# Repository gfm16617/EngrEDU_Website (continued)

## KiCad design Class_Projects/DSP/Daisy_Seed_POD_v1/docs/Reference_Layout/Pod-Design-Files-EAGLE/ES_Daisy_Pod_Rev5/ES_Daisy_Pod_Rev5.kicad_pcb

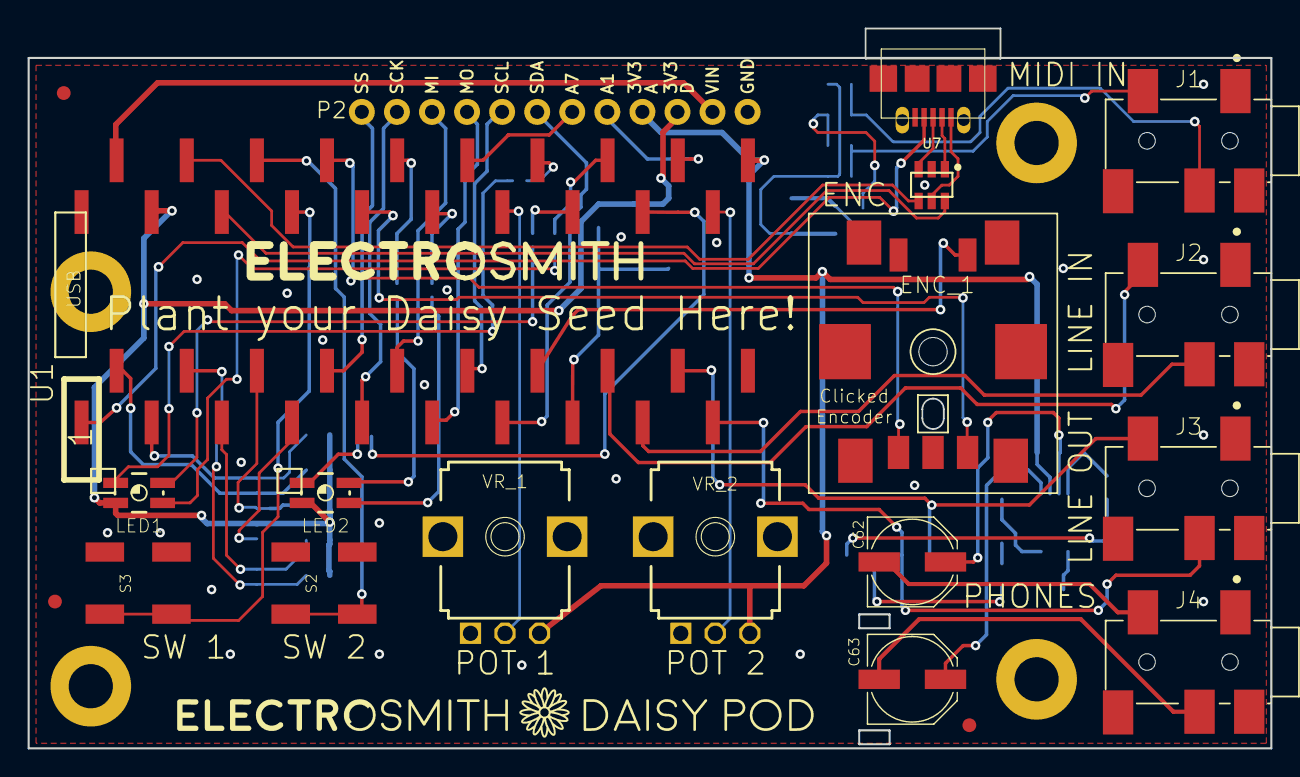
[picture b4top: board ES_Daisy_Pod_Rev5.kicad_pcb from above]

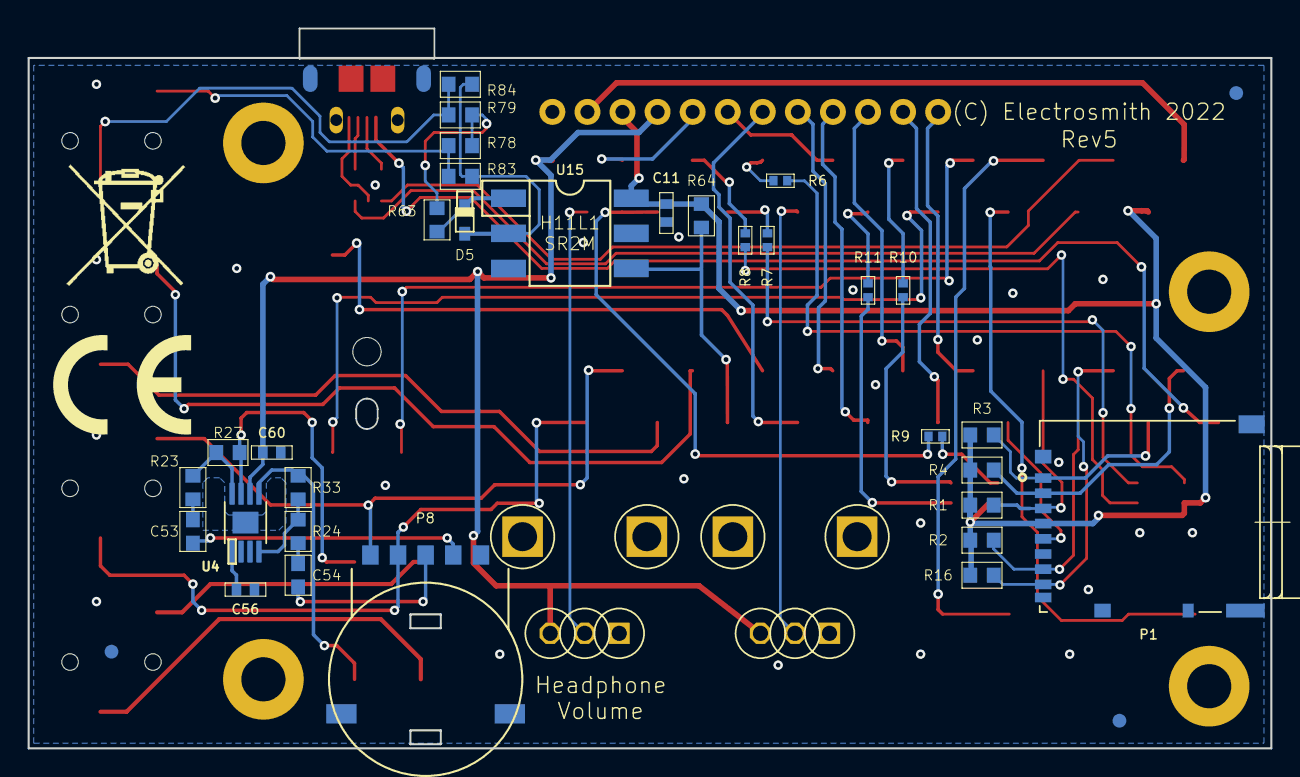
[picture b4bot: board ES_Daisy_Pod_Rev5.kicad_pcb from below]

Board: 2 copper layers, 90.0 x 52.1 mm, 62 parts (36 on the bottom side), 64 nets.

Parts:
C11, C56, C60: 100NF; C0402
C53, C54: 470NF; C0603
C62, C63: 100UF PANASONIC D8; PANASONIC_D
D5: NSR1020MW2T3G; SOD-323F
ENC_1: PEC11 Clicked Encoder; VH1-147
FD1, FD2, FD3, FD4, FD5, FD6: FIDUCIAL; FIDUCIAL_1MM
H1, H2, H3, H4: MOUNT-PAD-ROUND_3.2_NO_SILK; 32-PAD_NO_SILK
J1, J2, J3, J4: SMT Stereo 3.5mm Jack; CUI_SJ2-35863B1-SMT-TR
LED1, LED2: RGB LED SMT PLCC4; P-LCC-4-3
P1: SMT MICRO SD HORIZONTAL; HRS_DM3AT-SF-PEJM5
P2: M12_ALL_CIRCLE_DNI; 1X12_NO_SILK_ALL_CIRCLE
P5: USB MICRO SMT H-B; 47589-0001_CUT2
P8: SMT ROTARY DUAL GANG POT; RK10J12R0A0B
R1, R2, R3, R4, R16: 47K; R0603
R6, R7, R8, R9, R10, R11: 1K; R0402
R23, R24: 22K; R0603
R27, R33: 33K; R0603
R63: 220R; R0603
R64: 270R; R0603
R78, R84: DNI 0R; R0603
R79, R83: 0R; R0603
S2, S3: SMT Mini Button; TL3301SPF160QJ
U1: ES_DAISY_SEED_REV4_SMT; ES_DAISY_SEED_SMT
U4: TPA6110 MSOP-8; MSOP_8_PWRPAD
U7: USBLC6 TVS SOT-23-6; SOT-23-6L
U15: H11L1SR2M; DIL06_GULLWING
U$2: TONNE_9X13MM
U$3: CE_10X7.3MM
U$4: DAISY_POD_BRANDING_2
U$7: ES_TEXT_3X30MM
VR_1, VR_2: P-10K-B-R-PIP; 9MM_SNAP-IN_POT_SILK_PIP

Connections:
+3V3_A: C60.2, P2.9, U1.21, U4.6, VR_1.3, VR_2.3
+3V3_D: C11.1, LED1.2, LED2.2, P1.4, P2.10, R1.2, R2.2, R3.2, R4.2, R16.2, R64.1, U1.38, U15.6
A1: P2.8, U1.23
A7: P2.7, U1.29
AUDIO_IN_L: J2.2, U1.16
AUDIO_IN_R: J2.3, U1.17
AUDIO_OUT_L: J3.2, P8.P$5, U1.18
AUDIO_OUT_R: J3.3, P8.P$4, U1.19
ENC_A: ENC_1.A, U1.33
ENC_B: ENC_1.B, U1.32
ENC_CLICK: ENC_1.E, U1.14
GND: C11.2, C56.1, C60.1, ENC_1.C, ENC_1.D, J1.1, J2.1, J3.1, J4.1, P1.6, P1.P1, P1.P2, P1.P3, P1.P4, P1.SWB, P2.12, P5.5, P8.P$1, S2.3, S2.4, S3.3, S3.4, U1.20, U1.40, U4.2, U4.3, U4.9, U7.2, U15.5, VR_1.1, VR_2.1
HEADPHONE_OUT_L: C62.-, J4.2
HEADPHONE_OUT_R: C63.-, J4.3
HEADPHONE_WIPER_L: C53.1, P8.P$2
HEADPHONE_WIPER_R: C54.1, P8.P$3
I2C_SCL: P2.5, U1.12
I2C_SDA: P2.6, U1.13
LED_1_B: R8.2, U1.25
LED_1_G: R7.2, U1.26
LED_1_R: R6.2, U1.27
LED_2_B: R11.2, U1.30
LED_2_G: R10.2, U1.31
LED_2_R: R9.2, U1.24
MIDI_IN_A: R63.2, R78.1, R79.1
MIDI_IN_B: D5.A, R83.1, R84.1, U15.2
MIDI_IN_RING: J1.3, R79.2, R84.2
MIDI_IN_TIP: J1.2, R78.2, R83.2
unnamed: LED1.1, R6.1
unnamed: LED1.4, R7.1
unnamed: LED1.3, R8.1
unnamed: LED2.1, R9.1
unnamed: LED2.4, R10.1
unnamed: LED2.3, R11.1
unnamed: C54.2, R24.2
unnamed: R23.1, R27.2, U4.8
unnamed: R24.1, R33.2, U4.4
unnamed: C53.2, R23.2
unnamed: C56.2, U4.1
unnamed: C62.+, R27.1, U4.7
unnamed: C63.+, R33.1, U4.5
unnamed: D5.C, R63.1, U15.1
POT_1: U1.28, VR_1.2
POT_2: U1.22, VR_2.2
SD_CK: P1.5, U1.7
SD_CMD: P1.3, R1.1, U1.6
SD_D0: P1.7, R2.1, U1.5
SD_D1: P1.8, R16.1, U1.4
SD_D2: P1.1, R3.1, U1.3
SD_D3: P1.2, R4.1, U1.2
SPI_MISO: P2.3, U1.10
SPI_MOSI: P2.4, U1.11
SPI_NSS: P2.1, U1.8
SPI_SCK: P2.2, U1.9
TAC_SWITCH_1: S3.1, S3.2, U1.34
TAC_SWITCH_2: S2.1, S2.2, U1.35
USART1_RX: R64.2, U1.15, U15.4
USB_OTG_FS_D+: U1.37, U7.4
USB_OTG_FS_D-: U1.36, U7.6
USB_OTG_FS_D_IN_+: P5.3, U7.3
USB_OTG_FS_D_IN_-: P5.2, U7.1
USB_OTG_FS_ID: P5.4, U1.1
USB_VBUS: P5.1, U7.5
VIN: P2.11, U1.39

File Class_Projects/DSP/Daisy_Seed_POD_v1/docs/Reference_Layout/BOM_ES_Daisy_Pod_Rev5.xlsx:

Qty | IPN | MPN | Manufacturer | Designators | Vendor Link
5 | 47K R0603 | RC0603FR-0747KL | Yageo | R3 R4 R1 R2 R16 | Mouser
1 | USB MICRO SMT H-B | 47589-0001 | Molex | P5 | Mouser
2 | SMT Mini Button | TL3301SPF160QJ | E-Switch | S2 S3 | Mouser
1 | 220R R0603 | RC0603FR-07220RL | Yageo | R63 | Mouser
1 | 270R R0603 | CRCW0603270RFKEAC | Vishay | R64 | Mouser
3 | 100NF C0402 | CC0402KPX5R8BB104 | Yageo | C11 C56 C60 | Mouser
2 | 470NF C0603 | CL10B474KA8NFNC | Samsung | C53 C54 | Mouser
2 | 22K R0603 | RC0603FR-0722KL | Yageo | R23 R24 | Mouser
2 | 33K R0603 | RC0603FR-1333KL | Yageo | R27 R33 | Mouser
2 | RGB LED SMT PLCC4 | CLVBA-FKA-CAEDH8BBB7a363 | Cree | LED1 LED2 | Mouser
6 | 1K R0402 | RC0402FR-131KL | Yageo | R6 R7 R8 R9 R10 R11 | Mouser
4 | 0R R0603 | AC0603FR-070RL | Yageo | R79 R83 R78 R84 | Mouser
1 | USBLC6 TVS SOT-23-6 | USBLC6-2SC6TR | ST Micro | U7 | DigiKey
1 | NSR1020MW2T3G | NSR1020MW2T3G | On Semi | D5 | Mouser
1 | OPTO ISOLATOR | H11L1SR2M | On Semi | U15 | Mouser
1 | TPA6110 MSOP-8 | TPA6110A2DGNR | Texas Instruments | U4 | Mouser
2 | 100UF PANASONIC D8 | EMVE350ARA101MF80G | Chemi-Co | C63 C62 | Mouser
1 | EC11 Detented SMT Encoder | PEC11J-9220F-H0015 | Bourns | ENC_1 | Mouser
4 | SMT-JACK-S-H-3.5 | SJ2-35863B1-SMT-TR | CUI | J2 J3 J4 J1 | Mouser
1 | SMT MICRO SD HORIZONTAL | DM3AT-SF-PEJM5 | Hirose | P1 | Mouser
2 | P-10K-B-R Pointer | R0904N-B10K,L-25KQ/LWS | Song Huei | VR_1 VR_2 | Thonk
1 | 1X20 FEMALE SMT 2.54MM VERTICAL | SSM-120-L-SV | Samtec | U1 | Mouser
1 | SMT ROTARY DUAL GANG POT | RK10J12R0A0B | Alps | P8 | Mouser

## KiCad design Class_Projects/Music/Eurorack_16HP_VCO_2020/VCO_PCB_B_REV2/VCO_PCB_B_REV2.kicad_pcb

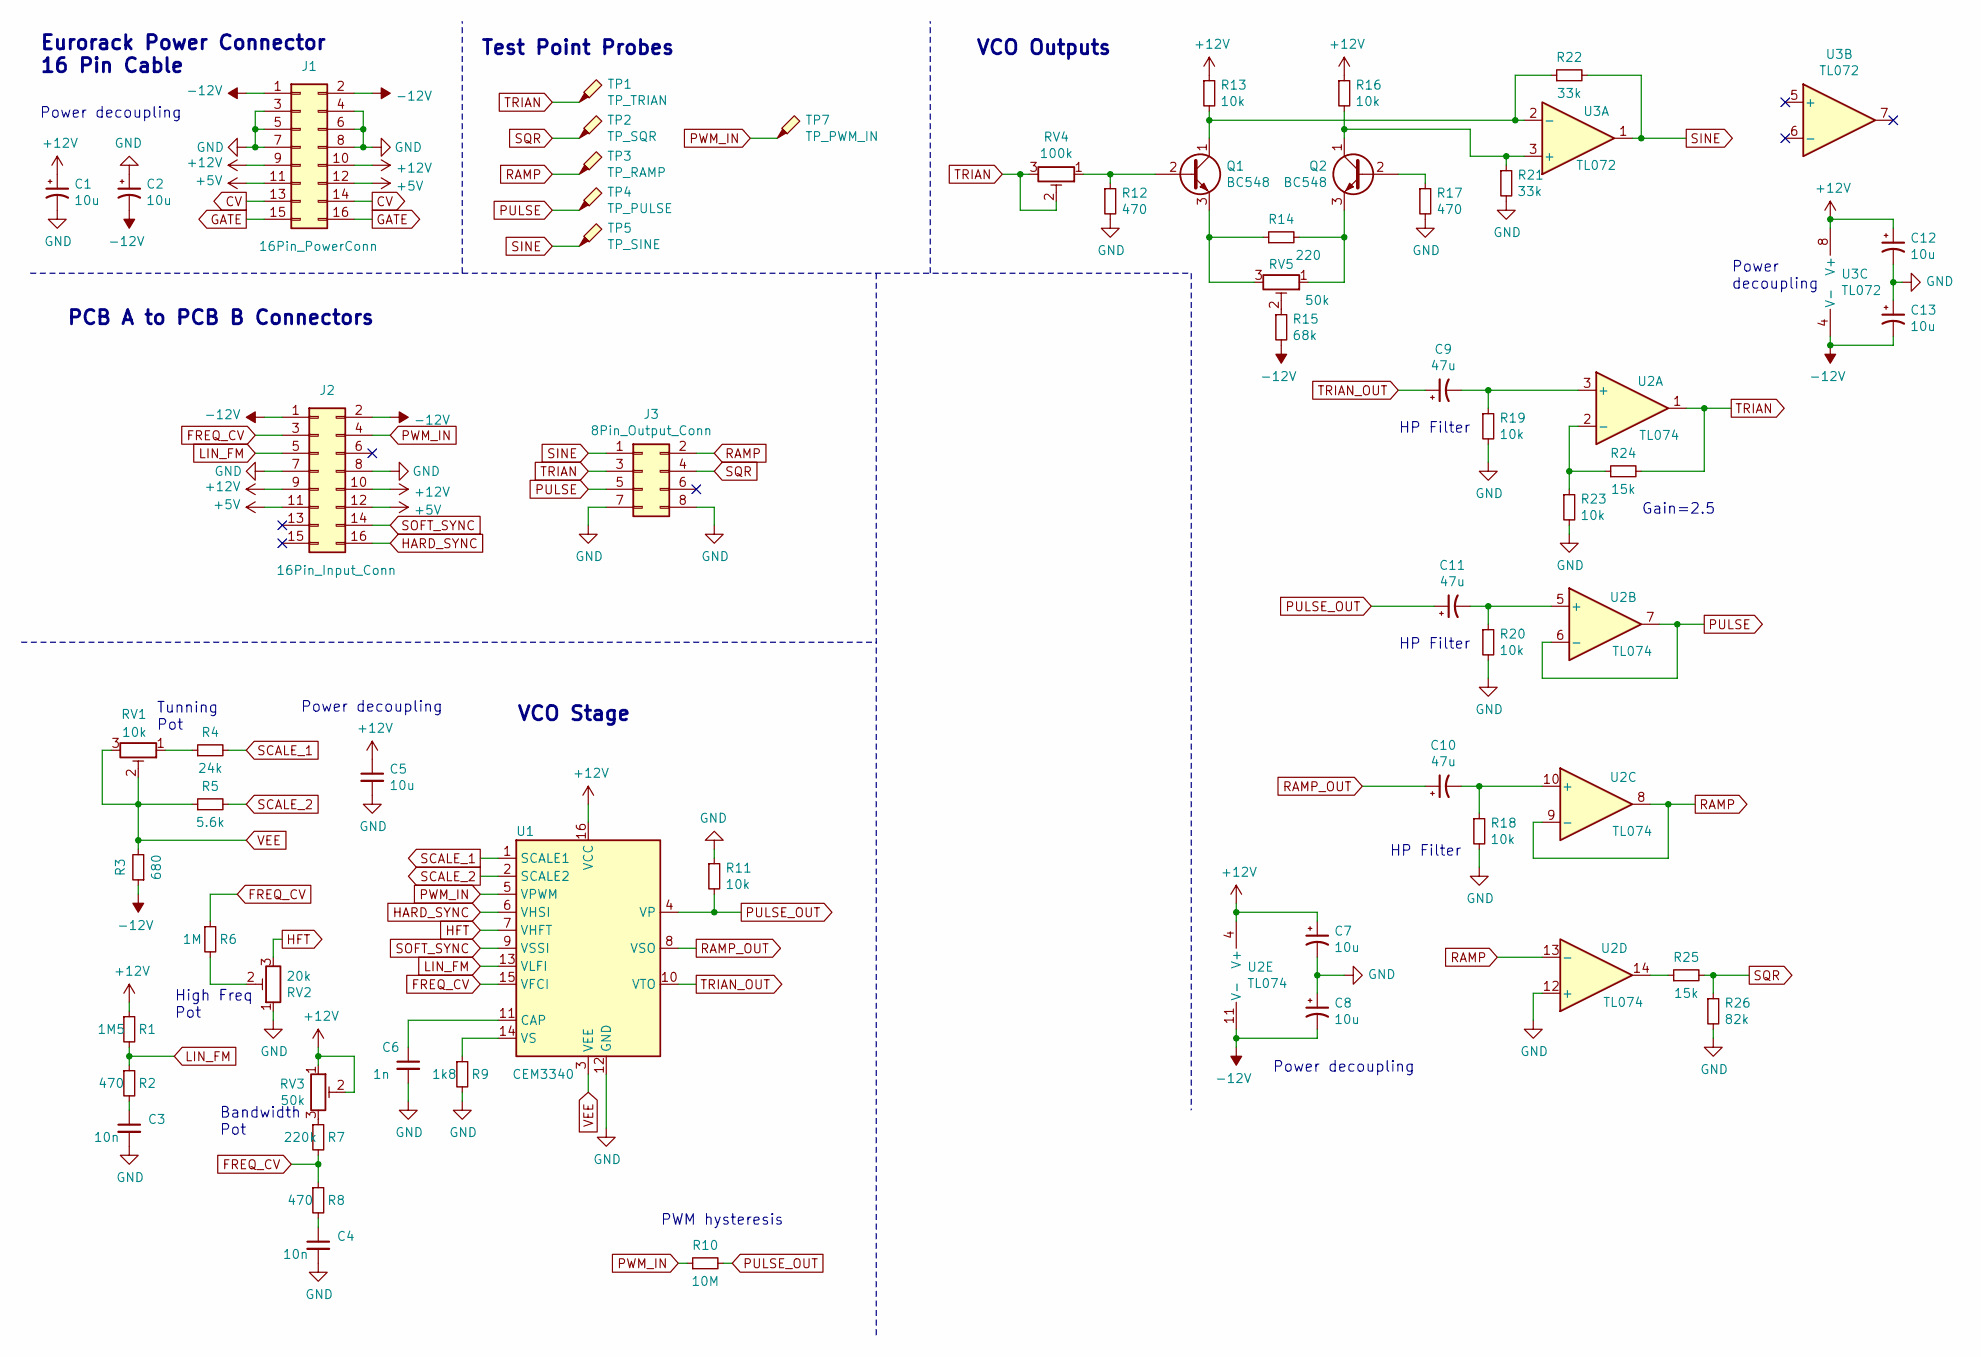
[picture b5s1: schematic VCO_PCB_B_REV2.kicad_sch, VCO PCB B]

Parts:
C1, C2, C7, C8, C12, C13: 10u; CP_Radial_D5.0mm_P2.50mm
C3, C4: 10n; C_Rect_L7.2mm_W3.0mm_P5.00mm_FKS2_FKP2_MKS2_MKP2
C5: 10u; C_Rect_L7.2mm_W3.0mm_P5.00mm_FKS2_FKP2_MKS2_MKP2
C6: 1n; C_Rect_L7.2mm_W3.0mm_P5.00mm_FKS2_FKP2_MKS2_MKP2
C9, C10, C11: 47u; CP_Radial_D4.0mm_P1.50mm
J1: 16Pin_PowerConn; IDC-Header_2x08_P2.54mm_Vertical
J2: 16Pin_Input_Conn; PinHeader_2x08_P2.54mm_Vertical
J3: 8Pin_Output_Conn; PinHeader_2x04_P2.54mm_Vertical
Q1, Q2: BC548; TO-92_Inline
R1: 1M5; R_Axial_DIN0207_L6.3mm_D2.5mm_P7.62mm_Horizontal
R2, R8, R12, R17: 470; R_Axial_DIN0207_L6.3mm_D2.5mm_P7.62mm_Horizontal
R3: 680; R_Axial_DIN0207_L6.3mm_D2.5mm_P7.62mm_Horizontal
R4: 24k; R_Axial_DIN0207_L6.3mm_D2.5mm_P7.62mm_Horizontal
R5: 5.6k; R_Axial_DIN0207_L6.3mm_D2.5mm_P7.62mm_Horizontal
R6: 1M; R_Axial_DIN0207_L6.3mm_D2.5mm_P7.62mm_Horizontal
R7: 220k; R_Axial_DIN0207_L6.3mm_D2.5mm_P7.62mm_Horizontal
R9: 1k8; R_Axial_DIN0207_L6.3mm_D2.5mm_P7.62mm_Horizontal
R10: 10M; R_Axial_DIN0207_L6.3mm_D2.5mm_P7.62mm_Horizontal
R11, R13, R16, R18, R19, R20, R23: 10k; R_Axial_DIN0207_L6.3mm_D2.5mm_P7.62mm_Horizontal
R14: 220; R_Axial_DIN0207_L6.3mm_D2.5mm_P7.62mm_Horizontal
R15: 68k; R_Axial_DIN0207_L6.3mm_D2.5mm_P7.62mm_Horizontal
R21, R22: 33k; R_Axial_DIN0207_L6.3mm_D2.5mm_P7.62mm_Horizontal
R24, R25: 15k; R_Axial_DIN0207_L6.3mm_D2.5mm_P7.62mm_Horizontal
R26: 82k; R_Axial_DIN0207_L6.3mm_D2.5mm_P7.62mm_Horizontal
RV1: 10k; Potentiometer_Bourns_3296Y_Vertical
RV2: 20k; Potentiometer_Bourns_3296Y_Vertical
RV3, RV5: 50k; Potentiometer_Bourns_3296Y_Vertical
RV4: 100k; Potentiometer_Bourns_3296Y_Vertical
TP1: TP_TRIAN; TestPoint_THTPad_D1.5mm_Drill0.7mm
TP2: TP_SQR; TestPoint_THTPad_D1.5mm_Drill0.7mm
TP3: TP_RAMP; TestPoint_THTPad_D1.5mm_Drill0.7mm
TP4: TP_PULSE; TestPoint_THTPad_D1.5mm_Drill0.7mm
TP5: TP_SINE; TestPoint_THTPad_D1.5mm_Drill0.7mm
TP7: TP_PWM_IN; TestPoint_THTPad_D1.5mm_Drill0.7mm
U1: CEM3340; DIP-16_W7.62mm_Socket
U2: TL074; DIP-14_W7.62mm_Socket
U3: TL072; DIP-8_W7.62mm_Socket

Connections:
+5V: J1.11, J1.12, J2.11, J2.12
+12V: C1.1, C5.1, C7.1, C12.1, J1.9, J1.10, J2.9, J2.10, R1.1, R13.1, R16.1, RV3.1, RV3.2, U1.16 (VCC), U2.4 (V+), U3.8 (V+)
-12V: C2.2, C8.2, C13.2, J1.1, J1.2, J2.1, J2.2, R3.1, R15.2, U2.11 (V-), U3.4 (V-)
CV: J1.13, J1.14
FREQ_CV: J2.3, R6.1, R7.2, R8.1, U1.15 (VFCI)
GATE: J1.15, J1.16
GND: C1.2, C2.1, C3.2, C4.2, C5.2, C6.2, C7.2, C8.1, C12.2, C13.1, J1.3, J1.4, J1.5, J1.6, J1.7, J1.8, J2.7, J2.8, J3.7, J3.8, R9.2, R11.1, R12.2, R17.2, R18.2, R19.2, R20.2, R21.2, R23.2, R26.2, RV2.1, U1.12 (GND), U2.12 (+)
HARD_SYNC: J2.16, U1.6 (VHSI)
HFT: RV2.3, U1.7 (VHFT)
LIN_FM: J2.5, R1.2, R2.1, U1.13 (VLFI)
unnamed: C3.1, R2.2
unnamed: C4.1, R8.2
unnamed: C6.1, U1.11 (CAP)
unnamed: C9.2, R19.1, U2.3 (+)
unnamed: C10.2, R18.1, U2.10 (+)
unnamed: C11.2, R20.1, U2.5 (+)
unnamed: Q1.1 (C), R13.2, R22.1, U3.2 (-)
unnamed: Q1.2 (B), R12.1, RV4.1
unnamed: Q1.3 (E), R14.1, RV5.3
unnamed: Q2.1 (C), R16.2, R21.1, U3.3 (+)
unnamed: Q2.2 (B), R17.1
unnamed: Q2.3 (E), R14.2, RV5.1
unnamed: R4.1, RV1.1
unnamed: R6.2, RV2.2
unnamed: R7.1, RV3.3
unnamed: R9.1, U1.14 (VS)
unnamed: R15.1, RV5.2
unnamed: R23.1, R24.1, U2.2 (-)
unnamed: R25.1, U2.14
PULSE: J3.5, TP4.1, U2.6 (-), U2.7
PULSE_OUT: C11.1, R10.2, R11.2, U1.4 (VP)
PWM_IN: J2.4, R10.1, TP7.1, U1.5 (VPWM)
RAMP: J3.2, TP3.1, U2.8, U2.9 (-), U2.13 (-)
RAMP_OUT: C10.1, U1.8 (VSO)
SCALE_1: R4.2, U1.1 (SCALE1)
SCALE_2: R5.2, U1.2 (SCALE2)
SINE: J3.1, R22.2, TP5.1, U3.1
SOFT_SYNC: J2.14, U1.9 (VSSI)
SQR: J3.4, R25.2, R26.1, TP2.1
TRIAN: J3.3, R24.2, RV4.2, RV4.3, TP1.1, U2.1
TRIAN_OUT: C9.1, U1.10 (VTO)
VEE: R3.2, R5.1, RV1.2, RV1.3, U1.3 (VEE)

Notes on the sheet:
HP Filter
Power decoupling
Gain=2.5
Bandwidth Pot
PCB A to PCB B Connectors
Test Point Probes
High Freq Pot
Tunning Pot
VCO Outputs
Eurorack Power Connector 16 Pin Cable
Power decoupling
PWM hysteresis
VCO Stage

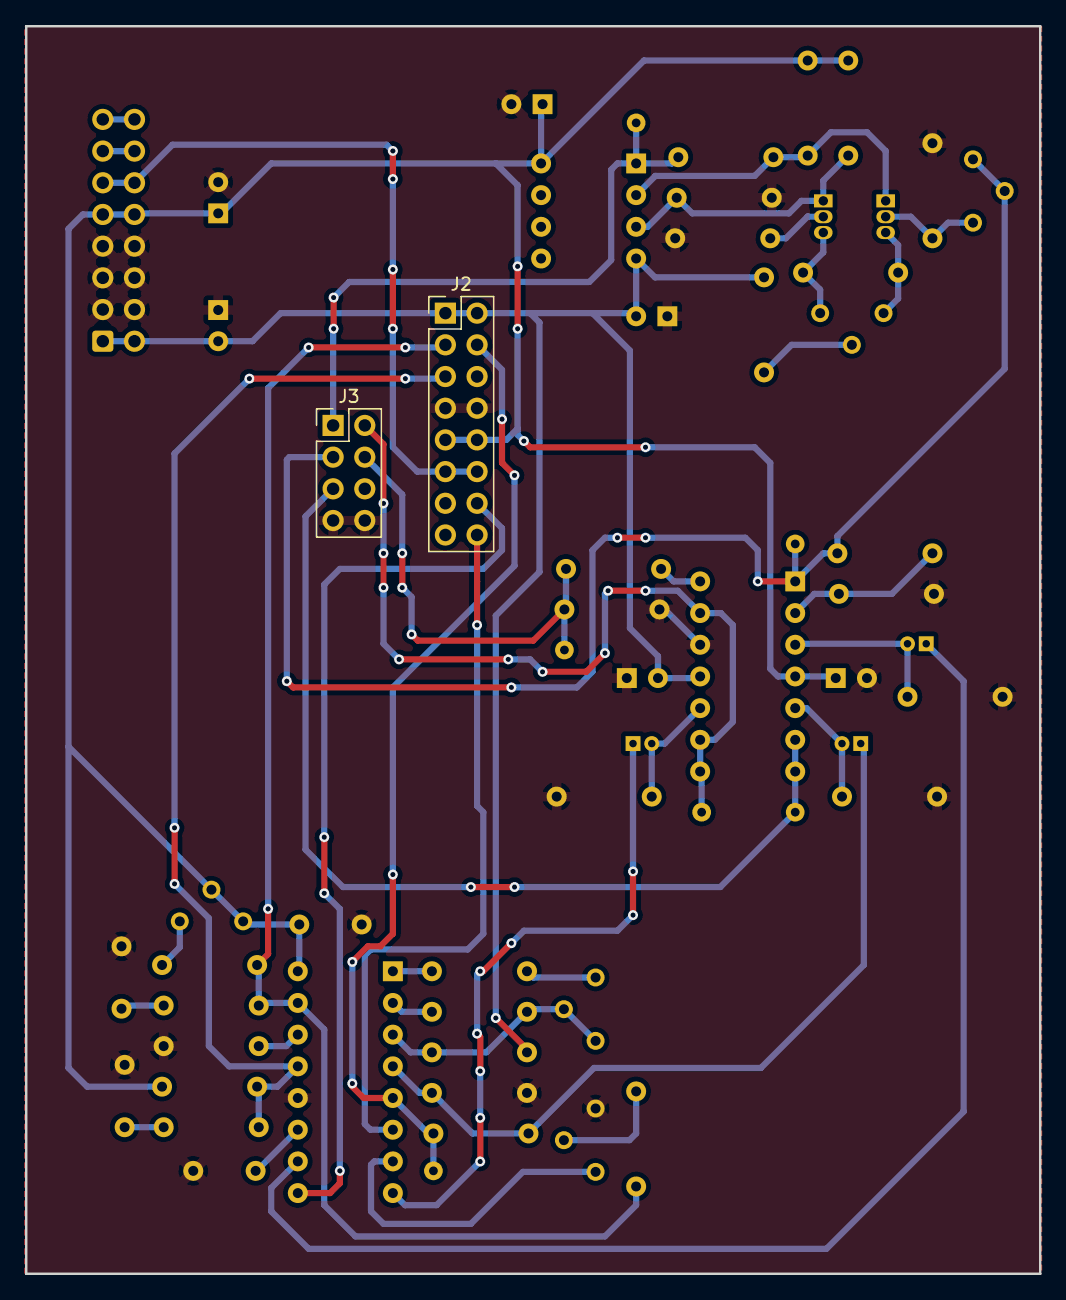
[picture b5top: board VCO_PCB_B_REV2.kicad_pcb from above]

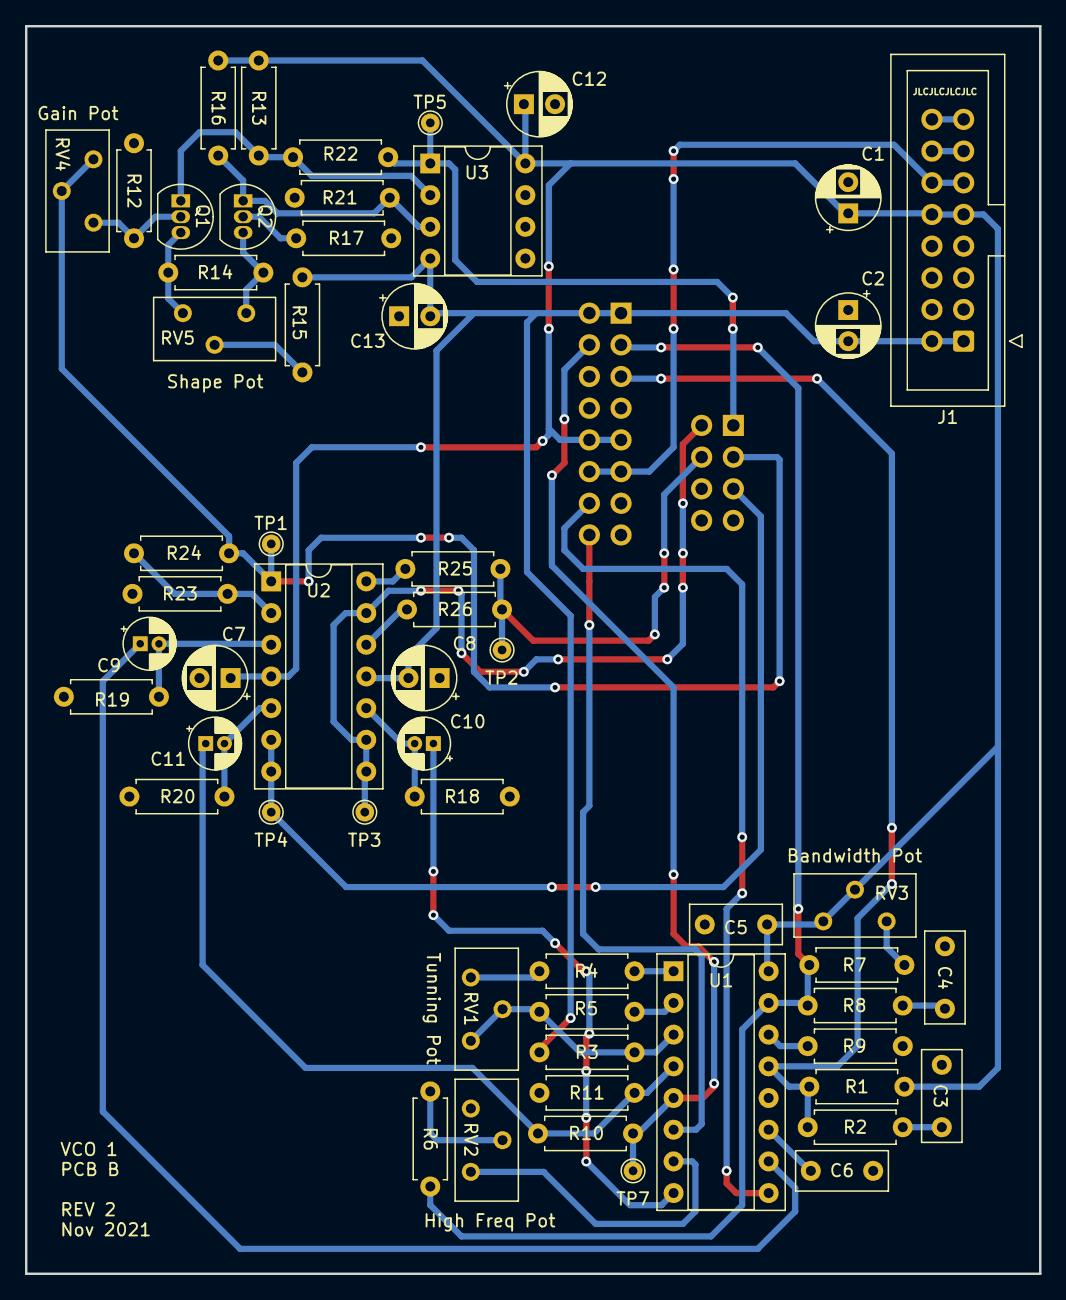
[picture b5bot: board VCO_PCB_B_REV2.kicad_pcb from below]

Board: 2 copper layers, 81.3 x 100.0 mm, 58 parts (56 on the bottom side), 42 nets.

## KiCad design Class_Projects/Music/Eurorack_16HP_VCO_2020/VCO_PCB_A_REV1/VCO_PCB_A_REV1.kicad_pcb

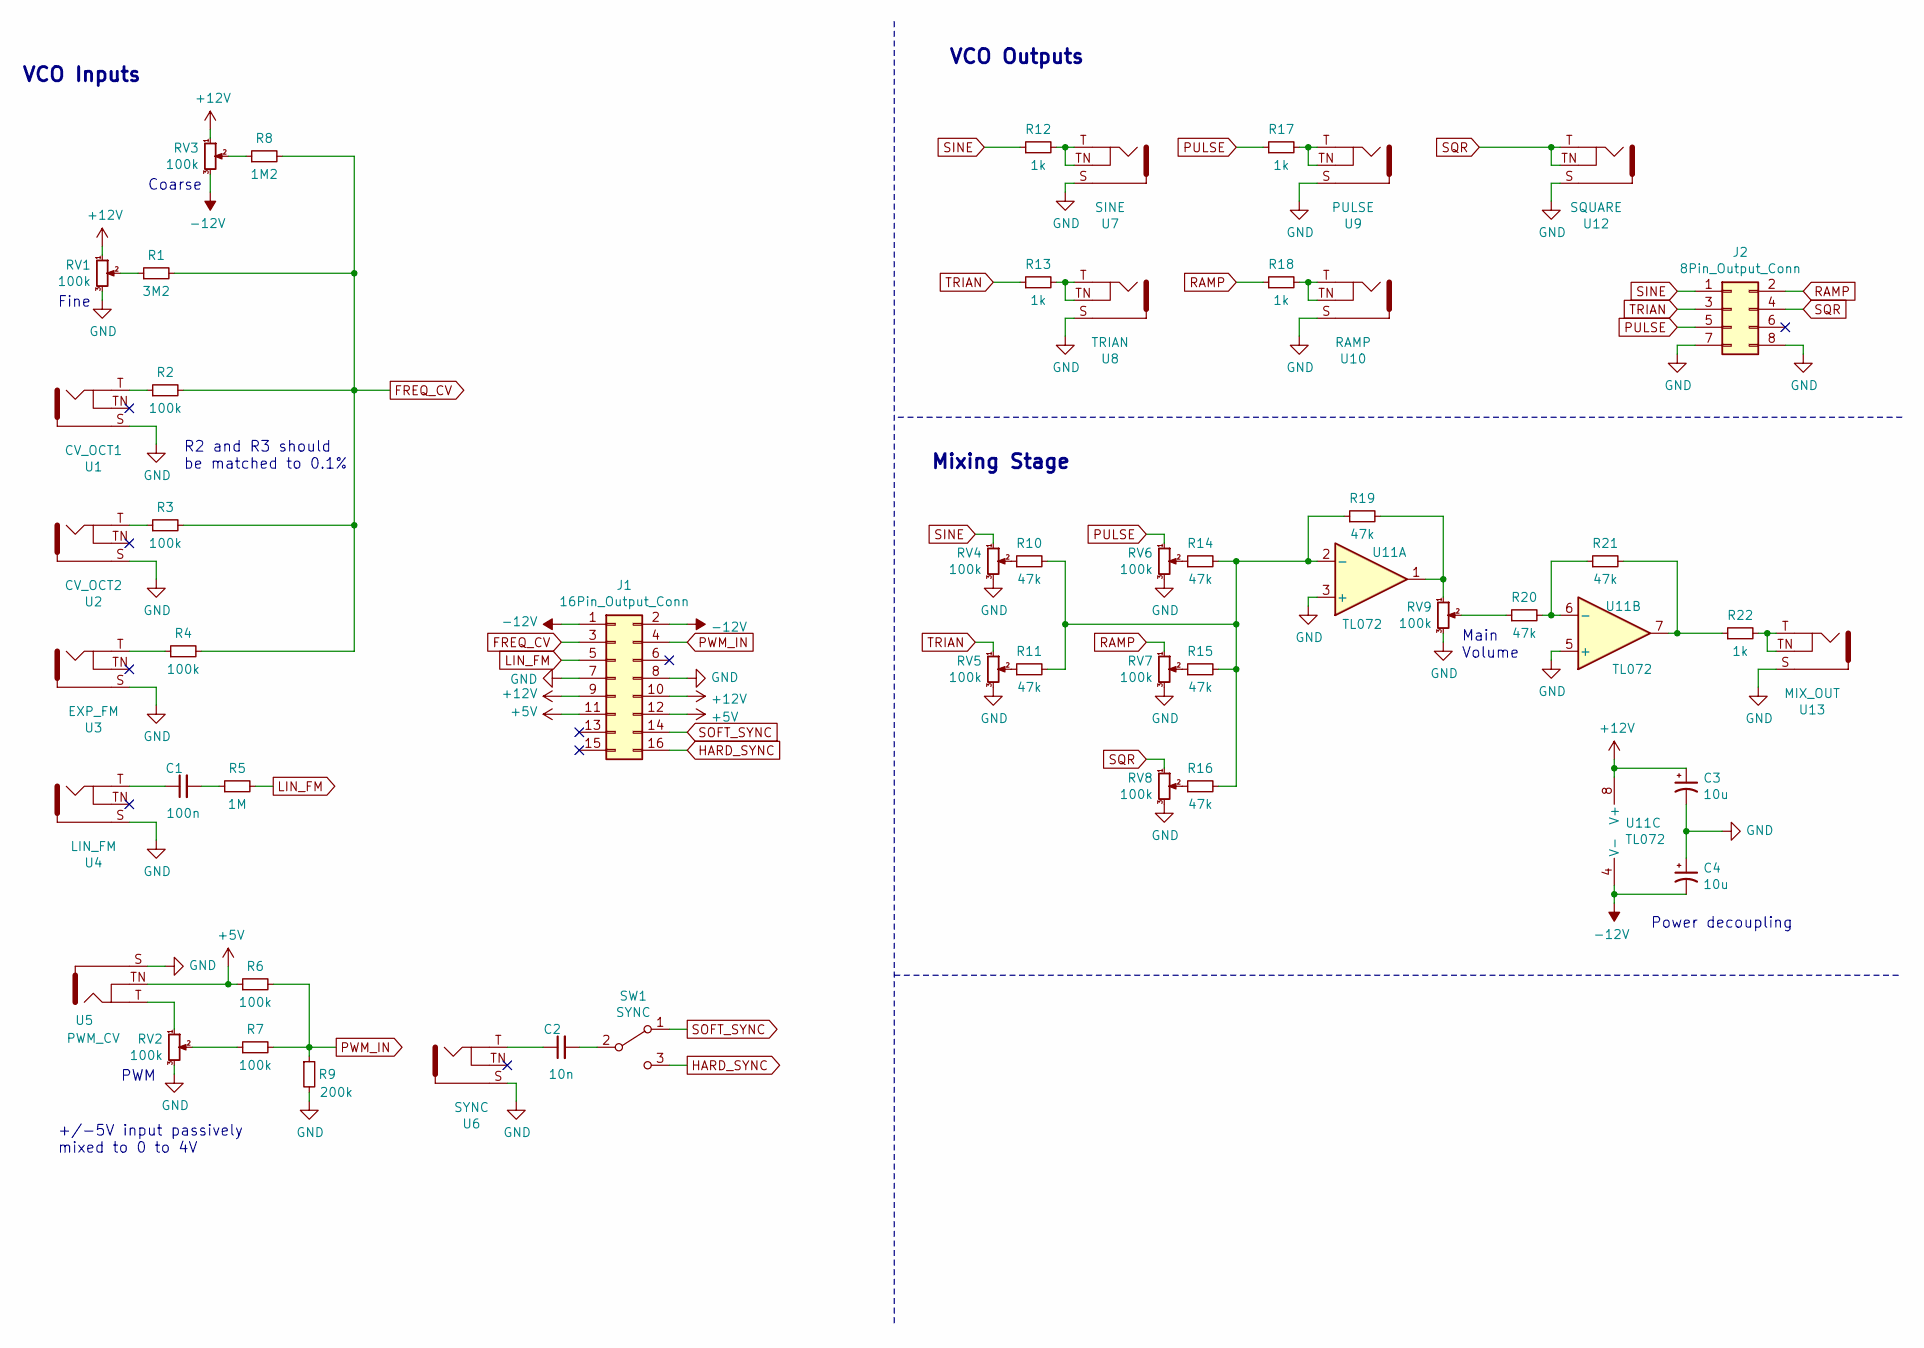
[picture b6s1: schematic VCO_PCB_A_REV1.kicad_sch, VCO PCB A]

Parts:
C1: 100n; C_Rect_L7.2mm_W3.0mm_P5.00mm_FKS2_FKP2_MKS2_MKP2
C2: 10n; C_Rect_L7.2mm_W3.0mm_P5.00mm_FKS2_FKP2_MKS2_MKP2
C3, C4: 10u; CP_Radial_D5.0mm_P2.50mm
J1: 16Pin_Output_Conn; PinSocket_2x08_P2.54mm_Vertical
J2: 8Pin_Output_Conn; PinSocket_2x04_P2.54mm_Vertical
R1: 3M2; R_Axial_DIN0207_L6.3mm_D2.5mm_P7.62mm_Horizontal
R2, R3, R4, R6, R7: 100k; R_Axial_DIN0207_L6.3mm_D2.5mm_P7.62mm_Horizontal
R5: 1M; R_Axial_DIN0207_L6.3mm_D2.5mm_P7.62mm_Horizontal
R8: 1M2; R_Axial_DIN0207_L6.3mm_D2.5mm_P7.62mm_Horizontal
R9: 200k; R_Axial_DIN0207_L6.3mm_D2.5mm_P7.62mm_Horizontal
R10, R11, R14, R15, R16, R19, R20, R21: 47k; R_Axial_DIN0207_L6.3mm_D2.5mm_P7.62mm_Horizontal
R12, R13, R17, R18, R22: 1k; R_Axial_DIN0207_L6.3mm_D2.5mm_P7.62mm_Horizontal
RV1, RV2, RV3, RV4, RV5, RV6, RV7, RV8, RV9: 100k; Potentiometer_Alps_RK09K_Single_Vertical
SW1: SYNC; SW_Toggle_Blue_wSlots
U1: CV_OCT1; Jack_3.5mm_QingPu_WQP-PJ398SM_Vertical
U2: CV_OCT2; Jack_3.5mm_QingPu_WQP-PJ398SM_Vertical
U3: EXP_FM; Jack_3.5mm_QingPu_WQP-PJ398SM_Vertical
U4: LIN_FM; Jack_3.5mm_QingPu_WQP-PJ398SM_Vertical
U5: PWM_CV; Jack_3.5mm_QingPu_WQP-PJ398SM_Vertical
U6: SYNC; Jack_3.5mm_QingPu_WQP-PJ398SM_Vertical
U7: SINE; Jack_3.5mm_QingPu_WQP-PJ398SM_Vertical
U8: TRIAN; Jack_3.5mm_QingPu_WQP-PJ398SM_Vertical
U9: PULSE; Jack_3.5mm_QingPu_WQP-PJ398SM_Vertical
U10: RAMP; Jack_3.5mm_QingPu_WQP-PJ398SM_Vertical
U11: TL072; DIP-8_W7.62mm_Socket
U12: SQUARE; Jack_3.5mm_QingPu_WQP-PJ398SM_Vertical
U13: MIX_OUT; Jack_3.5mm_QingPu_WQP-PJ398SM_Vertical

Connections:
+5V: J1.11, J1.12, R6.1, U5.TN
+12V: C3.1, J1.9, J1.10, RV1.1, RV3.1, U11.8 (V+)
-12V: C4.2, J1.1, J1.2, RV3.3, U11.4 (V-)
FREQ_CV: J1.3, R1.2, R2.2, R3.2, R4.2, R8.2
GND: C3.2, C4.1, J1.7, J1.8, J2.7, J2.8, R9.2, RV1.3, RV2.3, RV4.3, RV5.3, RV6.3, RV7.3, RV8.3, RV9.3, U1.S, U2.S, U3.S, U4.S, U5.S, U6.S, U7.S, U8.S, U9.S, U10.S, U11.3 (+), U11.5 (+), U12.S, U13.S
HARD_SYNC: J1.16, SW1.3 (C)
LIN_FM: J1.5, R5.2
unnamed: C1.1, U4.T
unnamed: C1.2, R5.1
unnamed: C2.1, U6.T
unnamed: C2.2, SW1.2 (B)
unnamed: R1.1, RV1.2
unnamed: R2.1, U1.T
unnamed: R3.1, U2.T
unnamed: R4.1, U3.T
unnamed: R7.1, RV2.2
unnamed: R8.1, RV3.2
unnamed: R10.1, RV4.2
unnamed: R10.2, R11.2, R14.2, R15.2, R16.2, R19.1, U11.2 (-)
unnamed: R11.1, RV5.2
unnamed: R12.2, U7.T, U7.TN
unnamed: R13.2, U8.T, U8.TN
unnamed: R14.1, RV6.2
unnamed: R15.1, RV7.2
unnamed: R16.1, RV8.2
unnamed: R17.2, U9.T, U9.TN
unnamed: R18.2, U10.T, U10.TN
unnamed: R19.2, RV9.1, U11.1
unnamed: R20.1, RV9.2
unnamed: R20.2, R21.1, U11.6 (-)
unnamed: R21.2, R22.1, U11.7
unnamed: R22.2, U13.T, U13.TN
unnamed: RV2.1, U5.T
PULSE: J2.5, R17.1, RV6.1
PWM_IN: J1.4, R6.2, R7.2, R9.1
RAMP: J2.2, R18.1, RV7.1
SINE: J2.1, R12.1, RV4.1
SOFT_SYNC: J1.14, SW1.1 (A)
SQR: J2.4, RV8.1, U12.T, U12.TN
TRIAN: J2.3, R13.1, RV5.1

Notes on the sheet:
VCO Outputs
Fine
Main Volume
+/-5V input passively mixed to 0 to 4V
Mixing Stage
Power decoupling
VCO Inputs
R2 and R3 should be matched to 0.1%
Coarse
PWM

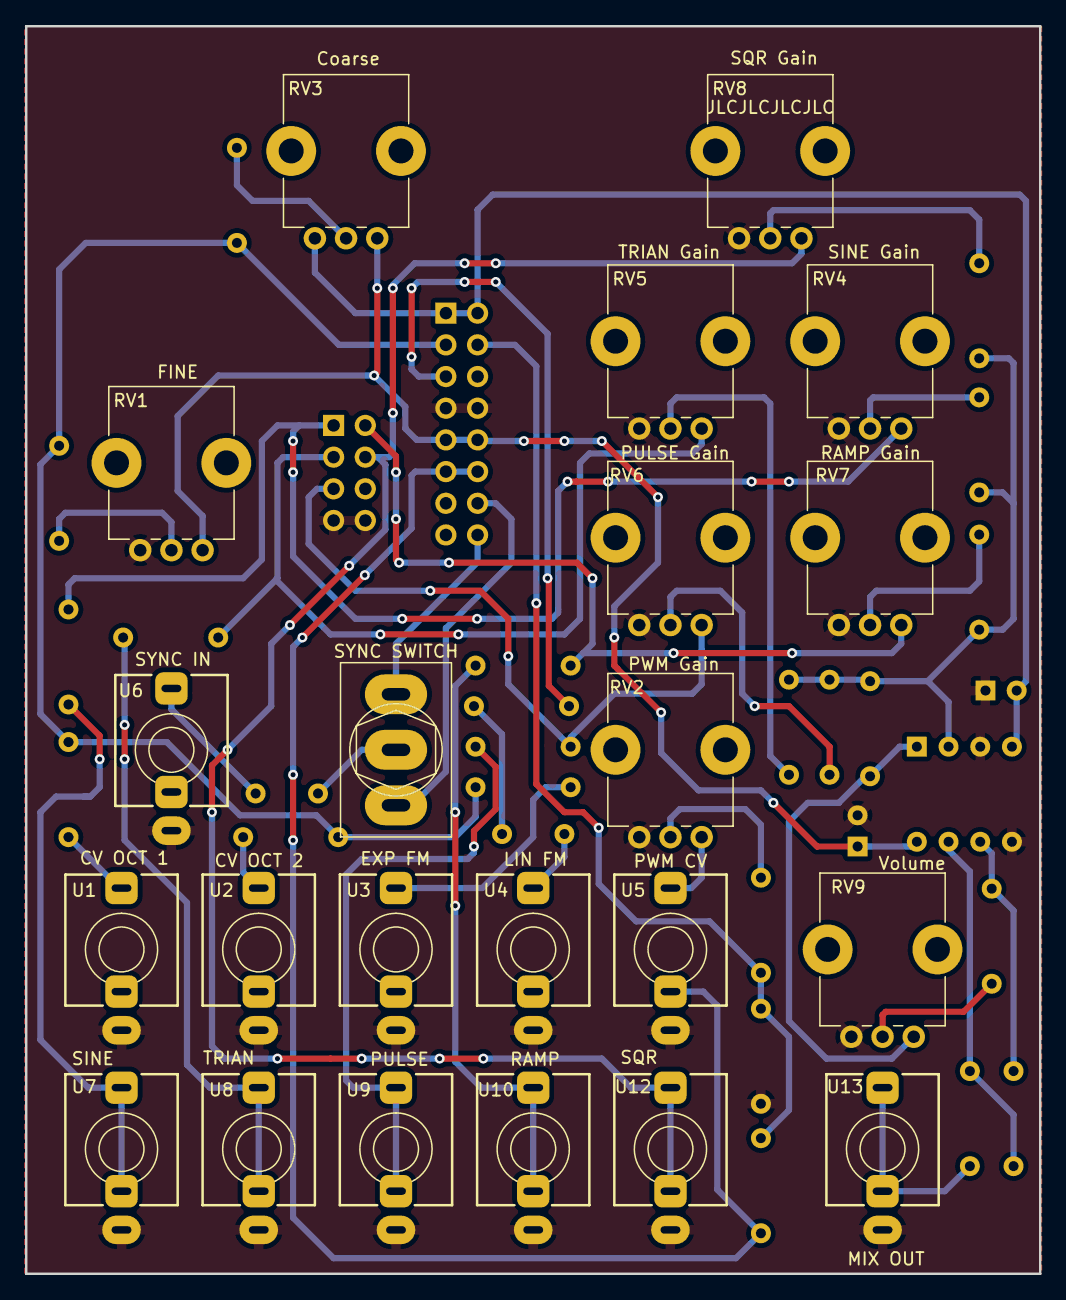
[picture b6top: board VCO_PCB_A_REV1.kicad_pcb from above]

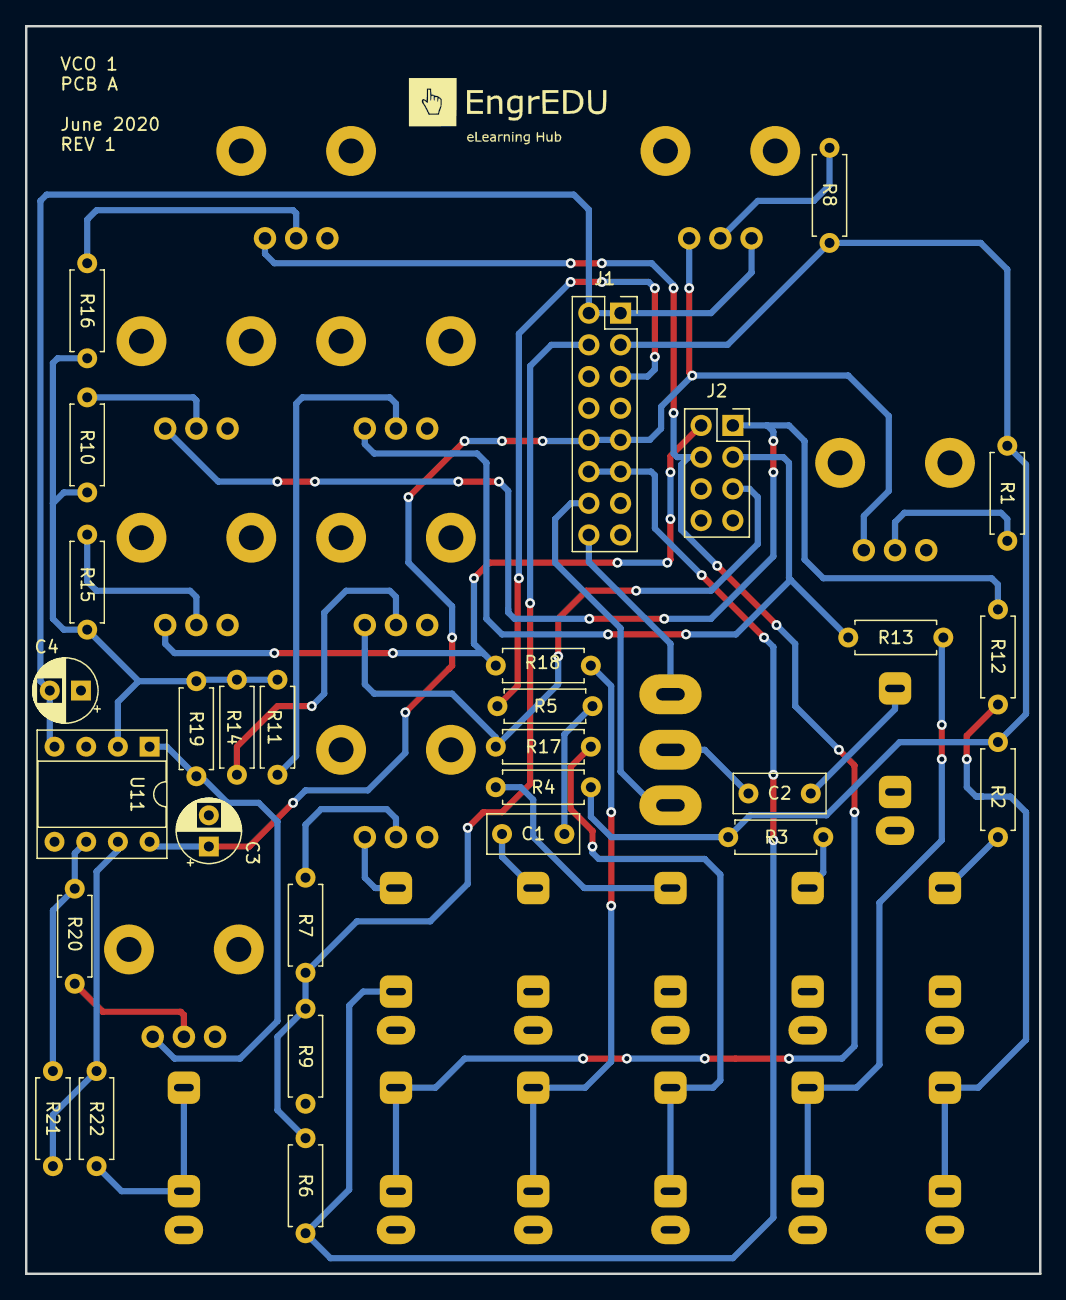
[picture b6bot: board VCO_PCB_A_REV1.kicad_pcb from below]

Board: 2 copper layers, 81.3 x 100.0 mm, 51 parts (29 on the bottom side), 40 nets.

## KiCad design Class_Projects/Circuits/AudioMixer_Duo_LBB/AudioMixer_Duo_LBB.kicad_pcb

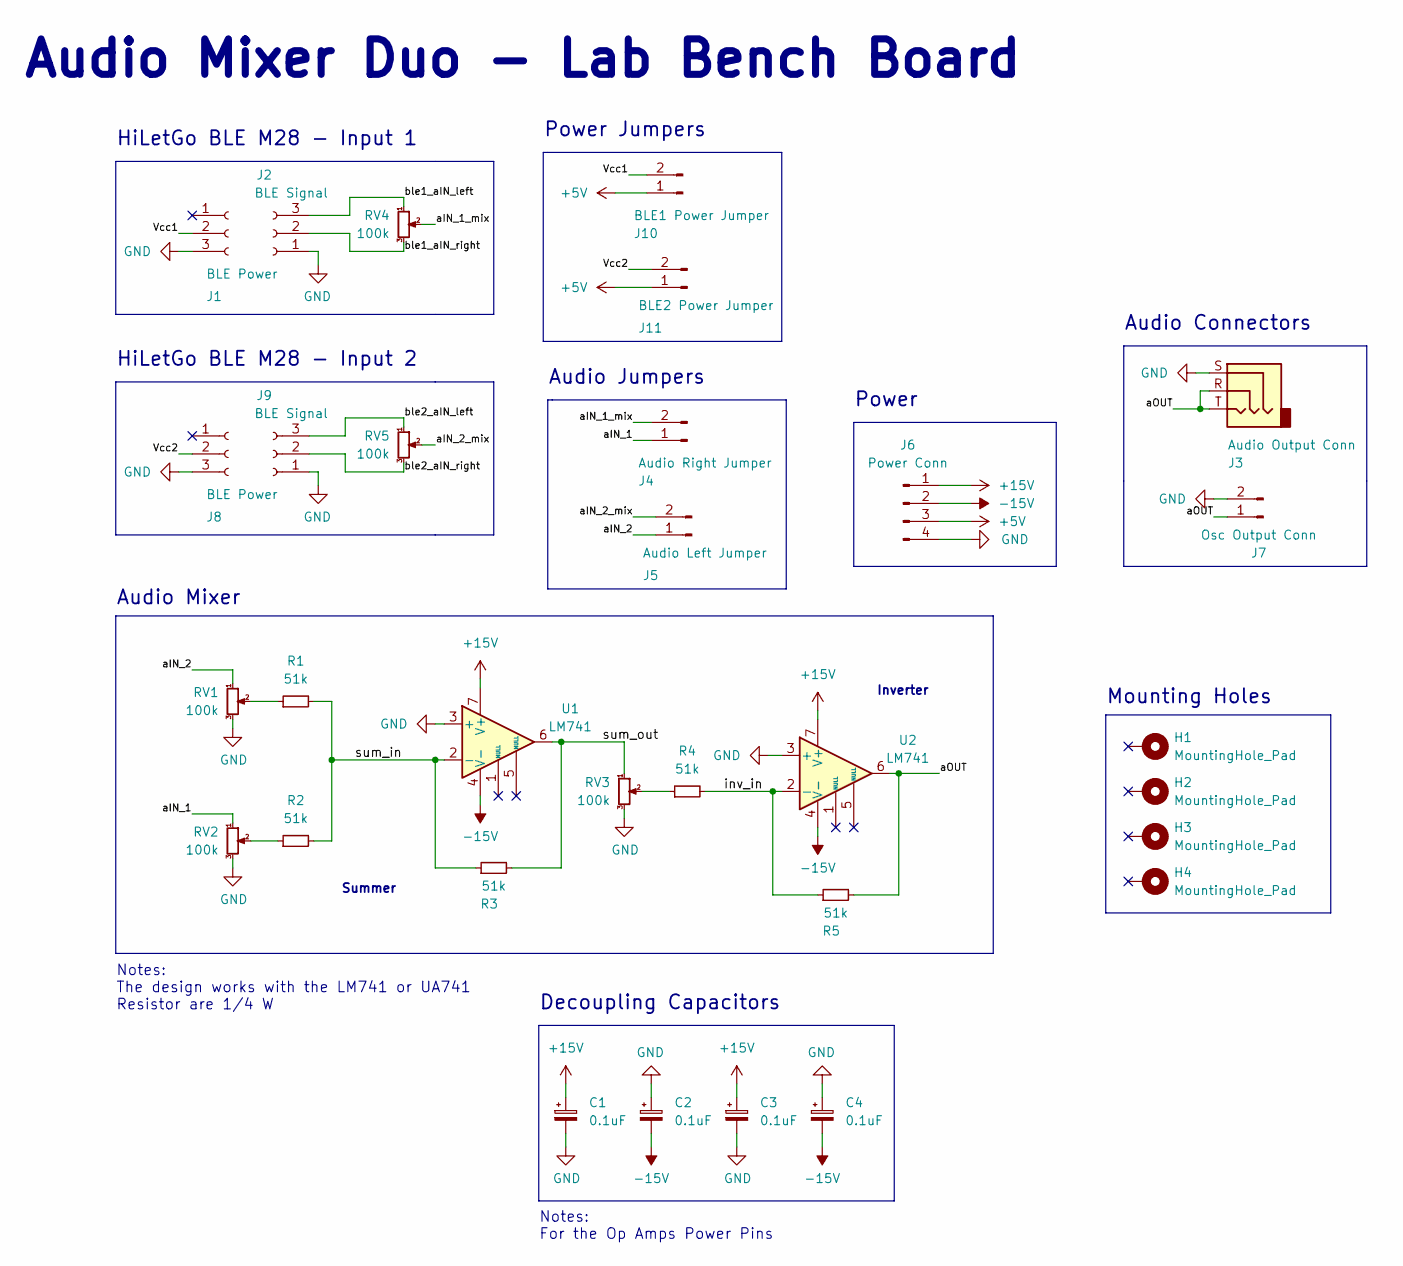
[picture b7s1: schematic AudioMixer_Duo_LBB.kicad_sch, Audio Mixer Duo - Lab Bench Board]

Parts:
C1, C2, C3, C4: 0.1uF; CP_Radial_D4.0mm_P1.50mm
H1, H2, H3, H4: MountingHole_Pad; MountingHole_3.2mm_M3_Pad_Via
J1, J8: BLE Power; PinSocket_1x03_P2.54mm_Vertical
J2, J9: BLE Signal; PinSocket_1x03_P2.54mm_Vertical
J3: Audio Output Conn; CUI_SJ1-3553NG
J4: Audio Right Jumper; PinHeader_1x02_P2.54mm_Vertical
J5: Audio Left Jumper; PinHeader_1x02_P2.54mm_Vertical
J6: Power Conn; PinHeader_1x04_P2.54mm_Vertical
J7: Osc Output Conn; PinHeader_1x02_P2.54mm_Vertical
J10: BLE1 Power Jumper; PinHeader_1x02_P2.54mm_Vertical
J11: BLE2 Power Jumper; PinHeader_1x02_P2.54mm_Vertical
R1, R2, R3, R4, R5: 51k; R_Axial_DIN0207_L6.3mm_D2.5mm_P10.16mm_Horizontal
RV1, RV2, RV3, RV4, RV5: 100k; Potentiometer_Alps_RK09K_Single_Vertical
U1, U2: LM741; DIP-8_W7.62mm_Socket_LongPads

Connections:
+5V: J6.3, J10.1, J11.1
+15V: C1.1, C3.1, J6.1, U1.7 (V+), U2.7 (V+)
-15V: C2.2, C4.2, J6.2, U1.4 (V-), U2.4 (V-)
/Vcc1: J1.2, J10.2
/Vcc2: J8.2, J11.2
/aIN_1: J4.1, RV2.1
/aIN_1_mix: J4.2, RV4.2
/aIN_2: J5.1, RV1.1
/aIN_2_mix: J5.2, RV5.2
/aOUT: J3.R, J3.T, J7.1, R5.2, U2.6
/ble1_aIN_left: J2.3, RV4.1
/ble1_aIN_right: J2.2, RV4.3
/ble2_aIN_left: J9.3, RV5.1
/ble2_aIN_right: J9.2, RV5.3
/inv_in: R4.2, R5.1, U2.2 (-)
/sum_in: R1.2, R2.2, R3.1, U1.2 (-)
/sum_out: R3.2, RV3.1, U1.6
GND: C1.2, C2.1, C3.2, C4.1, J1.3, J2.1, J3.S, J6.4, J7.2, J8.3, J9.1, RV1.3, RV2.3, RV3.3, U1.3 (+), U2.3 (+)
unnamed: R1.1, RV1.2
unnamed: R2.1, RV2.2
unnamed: R4.1, RV3.2

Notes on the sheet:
Inverter
Power Jumpers
HiLetGo BLE M28 - Input 2
Audio Jumpers
Mounting Holes
HiLetGo BLE M28 - Input 1
Audio Connectors
Decoupling Capacitors
Audio Mixer Duo - Lab Bench Board
Power
Notes: The design works with the LM741 or UA741 Resistor are 1/4 W
Audio Mixer
Summer
Notes: For the Op Amps Power Pins
